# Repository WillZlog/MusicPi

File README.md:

# MusicPi

A server + remote that plays music so I don't have to be on my phone or on my computer to listen to music.

It controls playback with no phone, or computer necessary, so you can relax and listen to music **without the temptation of screens**. The case and PCB are all custom designed, by [@WillZlog](https://www.github.com/WillZlog).

## Tech Stack

**Remote:** ESP32 S3, buttons, OLED

**Receiver Dongle:** ESP32-C3 Super Mini, USB A - USB C Cable

**Raspberry Pi:** Python, Serial Listener, Librespot/Spotify

**CAD:** Onshape, custom enclosure

## Features

**Radio Mode:** Streams songs directly from commercial-free internet radio stations like FIP (France Inter Paris) or TSF (Télégraphie Sans Fil), to give you the classic radio style

**Physical Remote:** A physical remote with a (soon toggleable) OLED screen, and buttons, for full control of your music

**Raspberry Pi Music Server:** A Raspberry Pi streaming the music directly to speakers, no phone necessary!

**Spotify Integration:** Connects seamlessly directly with Spotify, and shows up as a speaker in the devices section

**OLED Screen:** Toggleable OLED screen that allows for quick checking of what song is playing, or which radio station is on!

**Uninterrupted listening:** ESP-NOW and unicast create a delayless connection between dongle and remote!

**Headless Setup:** Runs headlessly after setup, with no monitor or keyboard required.

**Custom PCB and custom case:** Every part, from the PCB to the case, was designed by yours truly, millimeter by millimeter, ensuring an accurate fit!

## How It Works

1. User presses a button on the remote
2. The remote sends a plain-text ESP-NOW command to the ESP32-C3 receiver dongle
3. Data gets transferred from ESP32-C3 to Raspberry Pi via serial USB connection (could be wireless)
4. Python script, `music_controller.py`, reads the command and then through librespot controls playback accordingly
5. Music gets streamed through Bluetooth to connected speakers

## Roadmap

- Battery for the remote so it doesn't have to be constantly plugged in

- Deep Sleep to save battery life

- Smaller enclosure design

## Controls
- Next x3 opens service menu
- Prev x3 toggles screen
- Play/pause x3 toggles radio mode

## Media

### Remote Prototype

### CAD Designs

### PCB and Schematic

## Current Status

* Working
  * Pi server
  * Remote communication with server
  * OLED
  * Toggleable OLED
* Designed
  * Case
  * PCB
* In Progress
  * Better case design
* Planned
  * Battery system
  * Deep Sleep

## AI DISCLOSURE

I did use AI in the beginning of the project, but stopped and rewrote/refactored all of the AI code by the end. All PCB and CAD files AND documentation were done by me.

## Authors

- [@WillZlog](https://www.github.com/WillZlog)

## License

This project is licensed under the MIT License.

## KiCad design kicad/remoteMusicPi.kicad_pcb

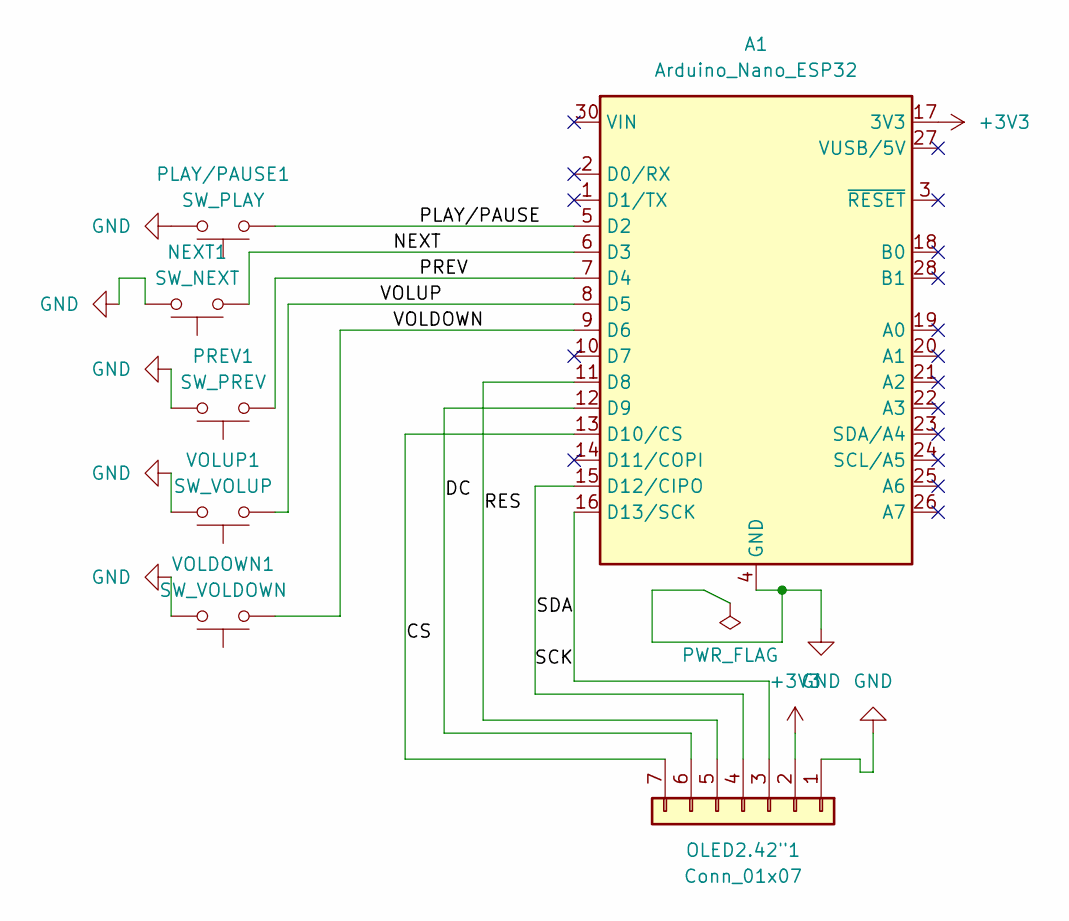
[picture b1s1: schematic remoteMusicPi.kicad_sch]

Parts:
A1: Arduino_Nano_ESP32; Arduino_Nano
NEXT1: SW_NEXT; SW_PUSH_6mm_H4.3mm
OLED2.42"1: Conn_01x07; PinSocket_1x07_P2.54mm_Vertical
PLAY/PAUSE1: SW_PLAY; SW_PUSH_6mm_H4.3mm
PREV1: SW_PREV; SW_PUSH_6mm_H4.3mm
VOLDOWN1: SW_VOLDOWN; SW_PUSH_6mm_H4.3mm
VOLUP1: SW_VOLUP; SW_PUSH_6mm_H4.3mm

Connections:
+3V3: A1.17 (3V3), OLED2.42"1.2
/CS: A1.13 (D10/CS), OLED2.42"1.7
/DC: A1.12 (D9), OLED2.42"1.6
/NEXT: A1.6 (D3), NEXT1.1
/PLAY/PAUSE: A1.5 (D2), PLAY/PAUSE1.1
/PREV: A1.7 (D4), PREV1.1
/RES: A1.11 (D8), OLED2.42"1.5
/SCK: A1.16 (D13/SCK), OLED2.42"1.3
/SDA: A1.15 (D12/CIPO), OLED2.42"1.4
/VOLDOWN: A1.9 (D6), VOLDOWN1.1
/VOLUP: A1.8 (D5), VOLUP1.1
GND: A1.4 (GND), A1.29 (GND), NEXT1.2, OLED2.42"1.1, PLAY/PAUSE1.2, PREV1.2, VOLDOWN1.2, VOLUP1.2

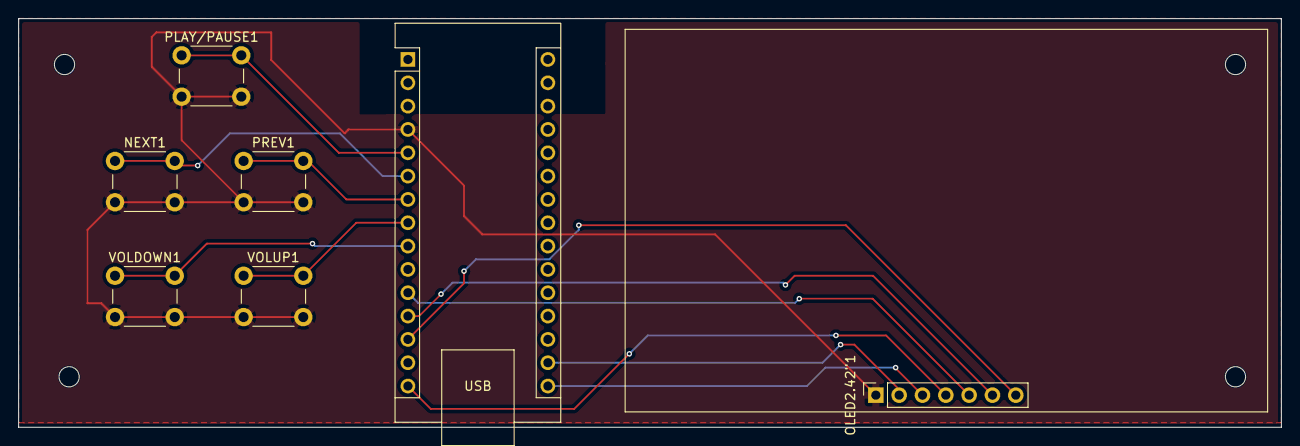
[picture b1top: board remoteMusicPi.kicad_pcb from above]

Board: 2 copper layers, 137.5 x 44.5 mm, 7 parts (0 on the bottom side), 12 nets.

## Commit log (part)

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2026-06-25 main commit w basically everything
2026-06-29 Updated README, removed unnecessary comments and improved code clarity in dongle_espnow_bridge.ino.
    Added new radio stations in music_controller.py, Enhanced button handling and UI features in remote_espnow.ino.
2026-06-29 Added media, updated readme to be moer specific and to include media, refactored firmware folder to have receiver, remote, and raspi folders, and added kicad files
2026-06-29 Feature: toggle OLED display on/off via remote control
2026-06-29 Updated remote firmware with refactoring and making it look better with more comments
2026-06-29 fixed CRITICAL error with how I refactored code, also added OLED timeout after 15 seconds of inactivity, with a switch in the service menu
2026-06-29 added a starup screen on boot, showing version number along wiht MusicPi
2026-06-29 Add GitHub Actions workflow for Arduino and python compilation
2026-06-29 restructured files to work with github actions
2026-06-29 tryna fix github actions
2026-06-29 Update arduino-compile.yml 2
2026-06-29 updating gitignore
2026-06-30 Added hardware.md and fixed version number in remote_espnow
2026-06-30 reformat 3d files, include images of PCB and SCH inside Kicad folder, add CODEOWNERS file
2026-06-30 Created bill of materials
2026-06-30 fixed error with version number
2026-06-30 added API endpoint <pi.local>:8000/ that returns current status NEED TO TEST
2026-06-30 added test button page to test button if they are working
2026-06-30 Revise security policy for supported versions and reporting
    Updated the security policy to reflect supported versions and reporting guidelines.
